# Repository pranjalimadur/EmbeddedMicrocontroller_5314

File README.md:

# EmbeddedMicrocontroller_5314
Embedded Microcontroller Systems 5314 Low Cost Programmable Pulse Generator with Automatic Level Controller

##Schematic for Pulse Generator

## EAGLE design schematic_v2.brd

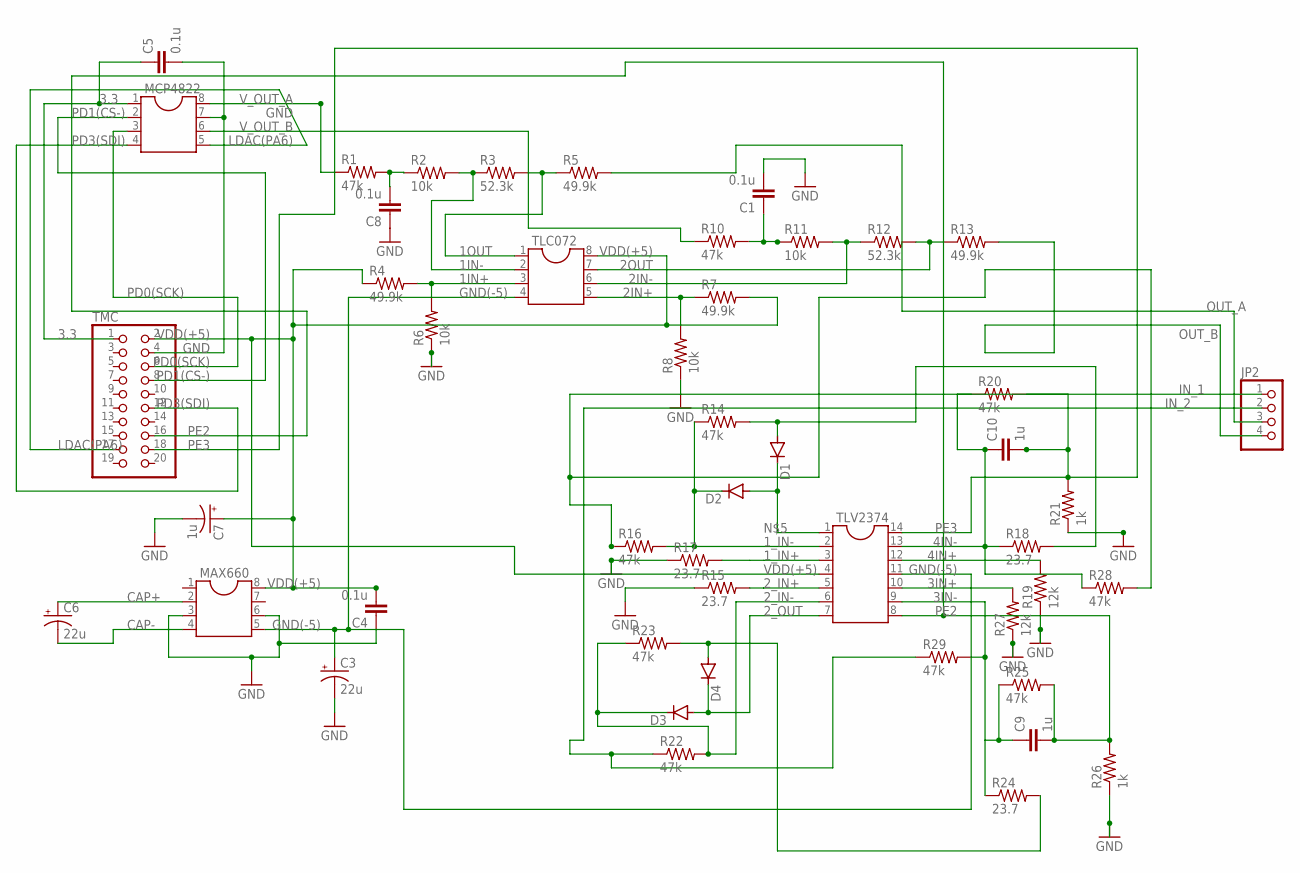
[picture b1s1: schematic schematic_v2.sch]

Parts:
C1, C4, C5, C8: 0.1u; C2.5-2
C3, C6: 22u; E2,5-6
C7: 1u; E2,5-6
C9, C10: 1u; C2.5-2
D1, D2, D3, D4: 1N4148DO35-7; DO35-7
JP2: PINHD-1X4; 1X04
MAX660: DIL8; DIL08
MCP4822: DIL8; DIL08
R1, R10, R14, R16, R20, R22, R23, R25, R28, R29: 47k; 0207/10
R2, R6, R8, R11: 10k; 0207/10
R3, R12: 52.3k; 0207/10
R4, R5, R7, R13: 49.9k; 0207/10
R15, R17, R18, R24: 23.7; 0207/10
R19, R27: 12k; 0207/10
R21, R26: 1k; 0207/10
TLC072: DIL8; DIL08
TLV2374: DIL14
TMC: PINHD-2X10; 2X10

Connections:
1IN+: R4.2, R6.2, TLC072.3
1IN-: R2.2, R3.1, TLC072.2
1OUT: R3.2, R5.1, TLC072.1
1_IN+: R17.2, TLV2374.3
1_IN-: D2.C, R14.1, R16.2, TLV2374.2
1_OUT: D1.A, R14.2, R18.2
2IN+: R7.1, R8.2, TLC072.5
2IN-: R11.2, R12.1, TLC072.6
2OUT: R12.2, R13.1, TLC072.7
2_IN+: R15.2, TLV2374.5
2_IN-: D3.C, R22.2, R23.1, TLV2374.6
2_OUT: D3.A, D4.C, TLV2374.7
3.3: C5.1, MCP4822.1, TMC.1
3IN+: R27.2, TLV2374.10
3IN-: C9.1, R24.1, R25.1, R29.2, TLV2374.9
4IN+: R19.2, TLV2374.12
4IN-: C10.1, R18.1, R20.1, R28.1, TLV2374.13
CAP+: C6.+, MAX660.2
CAP-: C6.-, MAX660.4
GND: C1.2, C3.-, C4.1, C5.2, C7.-, C8.1, MAX660.3, MAX660.6, MCP4822.7, R6.1, R8.1, R15.1, R17.1, R19.1, R21.1, R26.1, R27.1, TMC.4
GND(-5): C3.+, MAX660.5, TLC072.4, TLV2374.11
IN_1: JP2.1, R16.1, R28.2
IN_2: JP2.2, R22.1, R29.1
LDAC(PA6): MCP4822.5, TMC.17
unnamed: R10.2, R11.1
unnamed: C8.2, R1.2, R2.1
unnamed: D4.A, R23.2, R24.2
unnamed: D1.C, D2.A, TLV2374.1
OUT_A: JP2.3, R5.2
OUT_B: JP2.4, R13.2
PD0(SCK): MCP4822.3, TMC.6
PD1(CS-): MCP4822.2, TMC.8
PD3(SDI): MCP4822.4, TMC.12
PE2: C9.2, R25.2, R26.2, TLV2374.8, TMC.16
PE3: C10.2, R20.2, R21.2, TLV2374.14, TMC.18
VDD(+5): C4.2, C7.+, MAX660.8, R4.1, R7.2, TLC072.8, TLV2374.4, TMC.2
V_OUT_A: MCP4822.8, R1.1
V_OUT_B: MCP4822.6, R10.1

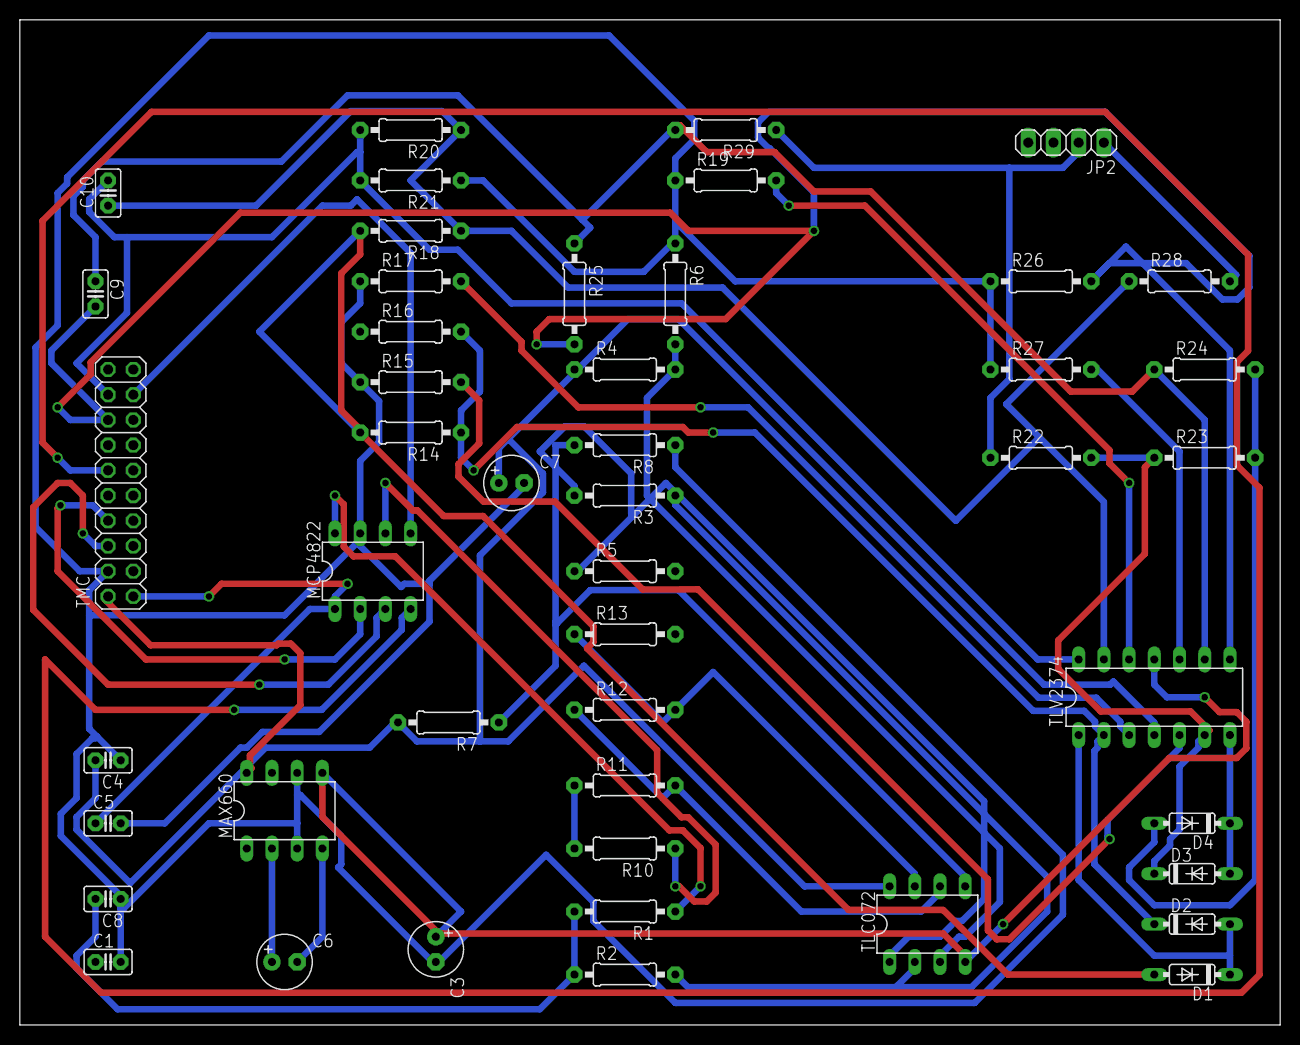
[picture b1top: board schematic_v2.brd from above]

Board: 2 copper layers, 127.0 x 101.3 mm, 47 parts (0 on the bottom side), 38 nets.

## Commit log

2021-02-11 Adding files and updating readme
